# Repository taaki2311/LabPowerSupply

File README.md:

# ECE_492-3_Topic_1

This git repository is for ECE/RS 492/3 Topic 1: Lab Power Supply in Spring to Fall 2022.

## Getting started

To make it easy for you to get started with GitLab, here's a list of recommended next steps.

Already a pro? Just edit this README.md and make it your own. Want to make it easy? [Use the template at the bottom](#editing-this-readme)!

## Add your files

- [ ] [Create](https://docs.gitlab.com/ee/user/project/repository/web_editor.html#create-a-file) or [upload](https://docs.gitlab.com/ee/user/project/repository/web_editor.html#upload-a-file) files
- [ ] [Add files using the command line](https://docs.gitlab.com/ee/gitlab-basics/add-file.html#add-a-file-using-the-command-line) or push an existing Git repository with the following command:

```
cd existing_repo
git remote add origin https://git.gmu.edu/tsingh8/ece_492-3_topic_1.git
git branch -M main
git push -uf origin main
```

## Integrate with your tools

- [ ] [Set up project integrations](https://git.gmu.edu/tsingh8/ece_492-3_topic_1/-/settings/integrations)

## Collaborate with your team

- [ ] [Invite team members and collaborators](https://docs.gitlab.com/ee/user/project/members/)
- [ ] [Create a new merge request](https://docs.gitlab.com/ee/user/project/merge_requests/creating_merge_requests.html)
- [ ] [Automatically close issues from merge requests](https://docs.gitlab.com/ee/user/project/issues/managing_issues.html#closing-issues-automatically)
- [ ] [Enable merge request approvals](https://docs.gitlab.com/ee/user/project/merge_requests/approvals/)
- [ ] [Automatically merge when pipeline succeeds](https://docs.gitlab.com/ee/user/project/merge_requests/merge_when_pipeline_succeeds.html)

## Test and Deploy

Use the built-in continuous integration in GitLab.

- [ ] [Get started with GitLab CI/CD](https://docs.gitlab.com/ee/ci/quick_start/index.html)
- [ ] [Analyze your code for known vulnerabilities with Static Application Security Testing(SAST)](https://docs.gitlab.com/ee/user/application_security/sast/)
- [ ] [Deploy to Kubernetes, Amazon EC2, or Amazon ECS using Auto Deploy](https://docs.gitlab.com/ee/topics/autodevops/requirements.html)
- [ ] [Use pull-based deployments for improved Kubernetes management](https://docs.gitlab.com/ee/user/clusters/agent/)
- [ ] [Set up protected environments](https://docs.gitlab.com/ee/ci/environments/protected_environments.html)

***

# Editing this README

When you're ready to make this README your own, just edit this file and use the handy template below (or feel free to structure it however you want - this is just a starting point!).  Thank you to [makeareadme.com](https://www.makeareadme.com/) for this template.

## Suggestions for a good README
Every project is different, so consider which of these sections apply to yours. The sections used in the template are suggestions for most open source projects. Also keep in mind that while a README can be too long and detailed, too long is better than too short. If you think your README is too long, consider utilizing another form of documentation rather than cutting out information.

## Name
Choose a self-explaining name for your project.

## Description
Let people know what your project can do specifically. Provide context and add a link to any reference visitors might be unfamiliar with. A list of Features or a Background subsection can also be added here. If there are alternatives to your project, this is a good place to list differentiating factors.

## Badges
On some READMEs, you may see small images that convey metadata, such as whether or not all the tests are passing for the project. You can use Shields to add some to your README. Many services also have instructions for adding a badge.

## Visuals
Depending on what you are making, it can be a good idea to include screenshots or even a video (you'll frequently see GIFs rather than actual videos). Tools like ttygif can help, but check out Asciinema for a more sophisticated method.

## Installation
Within a particular ecosystem, there may be a common way of installing things, such as using Yarn, NuGet, or Homebrew. However, consider the possibility that whoever is reading your README is a novice and would like more guidance. Listing specific steps helps remove ambiguity and gets people to using your project as quickly as possible. If it only runs in a specific context like a particular programming language version or operating system or has dependencies that have to be installed manually, also add a Requirements subsection.

## Usage
Use examples liberally, and show the expected output if you can. It's helpful to have inline the smallest example of usage that you can demonstrate, while providing links to more sophisticated examples if they are too long to reasonably include in the README.

## Support
Tell people where they can go to for help. It can be any combination of an issue tracker, a chat room, an email address, etc.

## Roadmap
If you have ideas for releases in the future, it is a good idea to list them in the README.

## Contributing
State if you are open to contributions and what your requirements are for accepting them.

For people who want to make changes to your project, it's helpful to have some documentation on how to get started. Perhaps there is a script that they should run or some environment variables that they need to set. Make these steps explicit. These instructions could also be useful to your future self.

You can also document commands to lint the code or run tests. These steps help to ensure high code quality and reduce the likelihood that the changes inadvertently break something. Having instructions for running tests is especially helpful if it requires external setup, such as starting a Selenium server for testing in a browser.

## Authors and acknowledgment
Show your appreciation to those who have contributed to the project.

## License
For open source projects, say how it is licensed.

## Project status
If you have run out of energy or time for your project, put a note at the top of the README saying that development has slowed down or stopped completely. Someone may choose to fork your project or volunteer to step in as a maintainer or owner, allowing your project to keep going. You can also make an explicit request for maintainers.

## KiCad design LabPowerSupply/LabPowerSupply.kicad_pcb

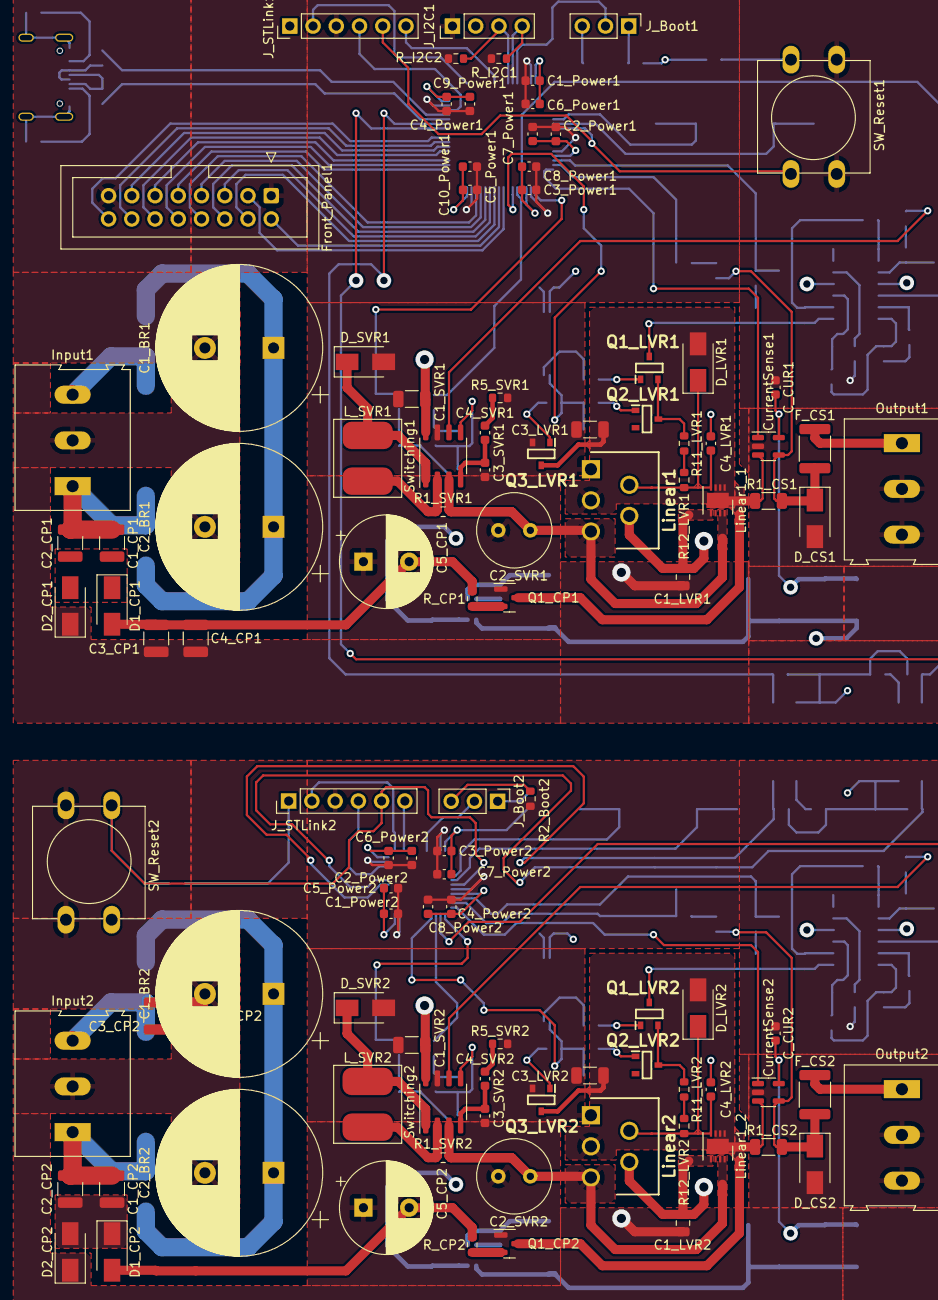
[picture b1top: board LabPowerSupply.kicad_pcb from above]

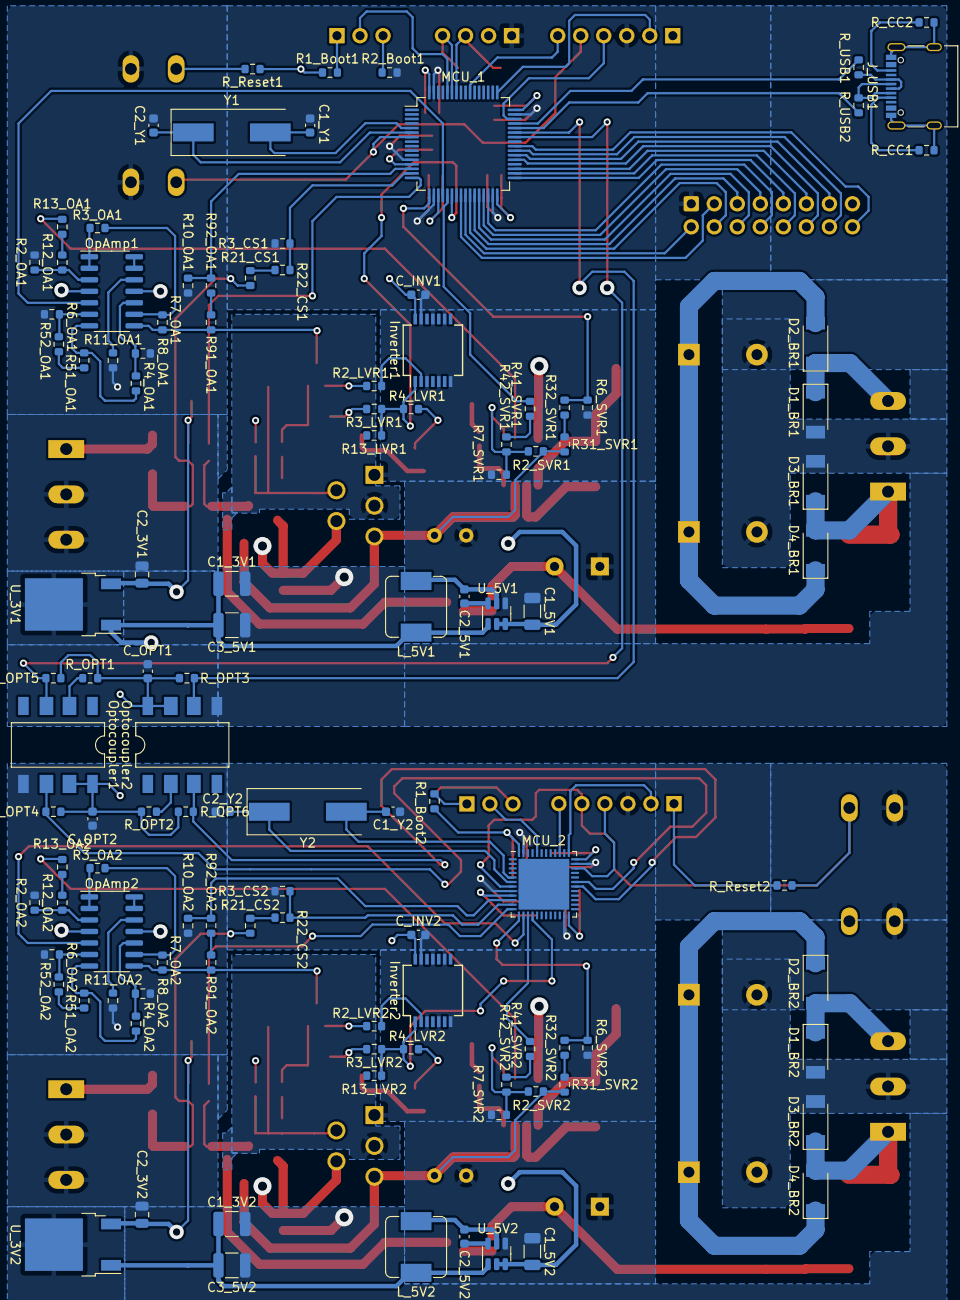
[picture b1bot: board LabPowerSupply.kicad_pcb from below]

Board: 4 copper layers, 219 parts (114 on the bottom side), 147 nets.

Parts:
C1_3V1, C1_3V2, C1_CP1, C1_CP2, C2_CP1, C2_CP2, C3_5V1, C3_5V2, C3_CP1, C3_CP2, C4_CP1, C4_CP2: 22u; C_1210_3225Metric
C1_5V1, C1_5V2, C1_SVR1, C1_SVR2, C3_LVR1, C3_LVR2: 10u; C_1206_3216Metric
C1_BR1, C1_BR2, C2_BR1, C2_BR2: 6.8m; CP_Radial_D18.0mm_P7.50mm
C1_LVR1, C1_LVR2: 4.7u; C_0805_2012Metric
C1_Power1, C1_Power2, C2_Power1, C2_Power2, C3_Power1, C3_Power2, C4_Power1, C4_Power2, C5_Power1: 1u; C_0603_1608Metric
C1_Y1, C1_Y2, C2_Y1, C2_Y2, C4_LVR1, C4_LVR2: 20p; C_0603_1608Metric
C2_3V1, C2_3V2: 2.2u; C_0805_2012Metric
C2_5V1, C2_5V2, C5_Power2, C6_Power1, C6_Power2, C7_Power1, C7_Power2, C8_Power1, C8_Power2, C9_Power1, C10_Power1: 100n; C_0603_1608Metric
C2_SVR1, C2_SVR2: 100u; C_Radial_D8.0mm_H7.0mm_P3.50mm
C3_SVR1, C3_SVR2: 22n; C_0603_1608Metric
C4_SVR1, C4_SVR2: 220p; C_0603_1608Metric
C5_CP1, C5_CP2: 1m; CP_Radial_D10.0mm_P5.00mm
C_CUR1, C_CUR2: 100n; C_0603_1608Metric
C_INV1, C_INV2: 100n; C_0603_1608Metric
C_OPT1, C_OPT2: 100n; C_0603_1608Metric
CurrentSense1, CurrentSense2: INA180A1; SOT-23-5
D1_BR1, D1_BR2, D2_BR1, D2_BR2, D3_BR1, D3_BR2, D4_BR1, D4_BR2: PMEG4050EP; D_SOD-128
D1_CP1, D1_CP2, D2_CP1, D2_CP2: 1N4001; D_SMA
D_CS1, D_CS2: 1N4001; D_SMA
D_LVR1, D_LVR2: 1N4001; D_SMA
D_SVR1, D_SVR2: 1N4001; D_SMA
F_CS1, F_CS2: 290m; Fuse_1812_4532Metric
Front_Panel1: Conn_02x08_Counter_Clockwise; IDC-Header_2x08_P2.54mm_Vertical
Input1, Input2: Screw_Terminal_01x03; TerminalBlock_Altech_AK300-3_P5.00mm
Inverter1, Inverter2: 74AHC04; SSOP-14_5.3x6.2mm_P0.65mm
J_Boot1, J_Boot2: Conn_01x03_Male; PinHeader_1x03_P2.54mm_Vertical
J_I2C1: Conn_01x04_Male; PinHeader_1x04_P2.54mm_Vertical
J_STLink1, J_STLink2: Conn_01x06_Male; PinHeader_1x06_P2.54mm_Vertical
J_USB1: USB_C_Receptacle_USB2.0; USB_C_Receptacle_Palconn_UTC16-G
L_5V1, L_5V2: 4.7u; L_Sumida_CDMC6D28_7.25x6.5mm
L_SVR1, L_SVR2: 22u; L_Sumida_CR75
Linear1, Linear2: LT3083ET#PBF; TO170P457X1022X2306-5P
Linear1_1, Linear1_2: LT3080xDD; DFN-8-1EP_3x3mm_P0.5mm_EP1.66x2.38mm
MCU_1: STM32L151R6TxA; LQFP-64_10x10mm_P0.5mm
MCU_2: STM32L100C6UxA; QFN-48-1EP_7x7mm_P0.5mm_EP5.6x5.6mm
OpAmp1, OpAmp2: LM324; SOIC-14_3.9x8.7mm_P1.27mm
Optocoupler1, Optocoupler2: 6N137; PowerIntegrations_SMD-8
Output1, Output2: Screw_Terminal_01x03; TerminalBlock_Altech_AK300-3_P5.00mm
Q1_CP1, Q1_CP2: FMMT495TA; SOT-23
Q1_LVR1, Q1_LVR2, Q2_LVR1, Q2_LVR2, Q3_LVR1, Q3_LVR2: PJA3404_R1_00001; SOT95P240X110-3N
R1_Boot1, R1_Boot2, R2_Boot1, R2_Boot2, R5_SVR1, R5_SVR2: 5.1k; R_0603_1608Metric
R1_CS1, R1_CS2: 300m; R_1206_3216Metric
R1_SVR1, R1_SVR2: 180m; R_0603_1608Metric
R2_LVR1, R2_LVR2, R2_OA1, R2_OA2, R3_CS1, R3_CS2, R3_LVR1, R3_LVR2, R3_OA1, R3_OA2, R4_LVR1, R4_LVR2, R4_OA1, R4_OA2, R6_OA1, R6_OA2, R6_SVR1, R6_SVR2, R7_OA1, R7_OA2, R8_OA1, R8_OA2, R10_OA1, R10_OA2, R22_CS1, R22_CS2, R92_OA1, R92_OA2: 1k; R_0603_1608Metric
R2_SVR1, R2_SVR2, R11_OA1, R11_OA2, R13_LVR1, R13_LVR2: 10k; R_0603_1608Metric
R7_SVR1, R7_SVR2, R41_SVR1, R41_SVR2, R42_SVR1, R42_SVR2: 1.2k; R_0603_1608Metric
R11_LVR1, R11_LVR2, R12_LVR1, R12_LVR2, R12_OA1, R12_OA2, R13_OA1, R13_OA2, R21_CS1, R21_CS2, R31_SVR1, R31_SVR2, R32_SVR1, R32_SVR2, R51_OA1, R51_OA2, R52_OA1, R52_OA2, R91_OA1, R91_OA2: 2k; R_0603_1608Metric
R_CC1, R_CC2: 5.1k; R_0603_1608Metric
R_CP1, R_CP2: 1k; R_0603_1608Metric
R_I2C1, R_I2C2: 4.7k; R_0603_1608Metric
R_OPT1, R_OPT2: 470; R_0603_1608Metric
R_OPT3, R_OPT4, R_OPT5, R_OPT6: 10k; R_0603_1608Metric
R_Reset1, R_Reset2: 1k; R_0603_1608Metric
R_USB1, R_USB2: 22; R_0603_1608Metric
SW_Reset1, SW_Reset2: SW_MEC_5G; SW_PUSH-12mm
Switching1, Switching2: L6902D; SO-8_3.9x4.9mm_P1.27mm
U_3V1, U_3V2: LP2950-3.3_TO252; TO-252-2
U_5V1, U_5V2: AP63205WU; TSOT-23-6
Y1, Y2: 8M; Crystal_SMD_HC49-SD

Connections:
+3.3V: C1_Power1.2, C2_3V1.1, C2_Power1.2, C3_Power1.2, C4_Power1.2, C5_Power1.2, C6_Power1.2, C7_Power1.2, C8_Power1.2, C9_Power1.2, C10_Power1.2, C_CUR1.2, C_INV1.2, C_OPT1.2, CurrentSense1.5 (V+), Inverter1.14 (VCC), J_STLink1.1, MCU_1.13 (VDDA), MCU_1.19 (VDD), MCU_1.32 (VDD), MCU_1.48 (VDD), MCU_1.64 (VDD), Optocoupler2.7 (EN), Optocoupler2.8 (VCC), R1_Boot1.2, R_OPT1.1, R_OPT3.2, R_OPT5.1, R_Reset1.1, U_3V1.3 (VO)
+3.3VA: C1_Power2.2, C2_3V2.1, C2_Power2.2, C3_Power2.2, C4_Power2.2, C5_Power2.2, C6_Power2.2, C7_Power2.2, C8_Power2.2, C_CUR2.2, C_INV2.2, C_OPT2.2, CurrentSense2.5 (V+), Inverter2.14 (VCC), J_STLink2.1, MCU_2.9 (VDDA), MCU_2.24 (VDD), MCU_2.36 (VDD), MCU_2.48 (VDD), Optocoupler1.7 (EN), Optocoupler1.8 (VCC), R1_Boot2.1, R_OPT2.2, R_OPT4.2, R_OPT6.2, R_Reset2.1, U_3V2.3 (VO)
/Channel 1 Power Rails/5 Volts: C1_3V1.2, C3_5V1.2, J_I2C1.2, L_5V1.2, U_3V1.1 (VI), U_5V1.1 (FB)
/Channel Power Supply 1/AC 1: D1_BR1.1 (K), D2_BR1.2 (A), Input1.3
/Channel Power Supply 1/AC 2: C1_CP1.1, C2_CP1.1, D3_BR1.1 (K), D4_BR1.2 (A), Input1.1
/Channel Power Supply 1/ADC 1: MCU_1.17 (PA3), R6_SVR1.1, R32_SVR1.2
/Channel Power Supply 1/ADC 2: MCU_1.14 (PA0), R10_OA1.1, R92_OA1.2
/Channel Power Supply 1/ADC 3: CurrentSense1.1, MCU_1.16 (PA2)
/Channel Power Supply 1/ADC 4: MCU_1.15 (PA1), R3_CS1.1, R22_CS1.2
/Channel Power Supply 1/Charge Pump/Charge: C3_LVR1.1, CurrentSense1.3 (+), D_LVR1.2 (A), Linear1.3 (OUT), Linear1_1.1 (OUT), Linear1_1.2 (OUT), Linear1_1.3 (OUT), Linear1_1.9 (OUT), Q1_CP1.3 (C), Q3_LVR1.3 (D), R1_CS1.1
/Channel Power Supply 1/Charge Pump/Negative: C3_CP1.1, C4_CP1.1, C5_CP1.2, D1_CP1.2 (A), OpAmp1.11 (V-), R_CP1.1
/Channel Power Supply 1/Current Sense /Output: CurrentSense1.4 (-), D_CS1.1 (K), F_CS1.1, R1_CS1.2, R21_CS1.1
/Channel Power Supply 1/DAC 1: MCU_1.21 (PA5), R41_SVR1.2
/Channel Power Supply 1/DAC 2: MCU_1.20 (PA4), OpAmp1.5 (+)
/Channel Power Supply 1/Differential Op-Amp Circuit/3.3 Volts: R13_OA1.1, Switching1.6 (VREF)
/Channel Power Supply 1/Differential Op-Amp Circuit/Set Voltage: OpAmp1.8, Q1_LVR1.3 (D), R7_OA1.2, R91_OA1.1
/Channel Power Supply 1/Linear Voltage Regulator /Linear Input: C2_SVR1.1, Linear1.5 (IN), Linear1_1.7 (IN), Linear1_1.8 (IN), R1_SVR1.2, R2_SVR1.1, R31_SVR1.1, Switching1.3 (CS-)
/Channel Power Supply 1/On/Off: Inverter1.1, MCU_1.22 (PA6), R3_LVR1.2, R4_LVR1.2, R13_LVR1.2
/Channel Power Supply 1/Switching Voltage Regulator/FeedBack: R2_SVR1.2, R7_SVR1.2, R42_SVR1.1, Switching1.5 (FB)
/Channel Power Supply 2/AC 1: D1_BR2.1 (K), D2_BR2.2 (A), Input2.3
/Channel Power Supply 2/AC 2: C1_CP2.1, C2_CP2.1, D3_BR2.1 (K), D4_BR2.2 (A), Input2.1
/Channel Power Supply 2/ADC 1: MCU_2.13 (PA3), R6_SVR2.1, R32_SVR2.2
/Channel Power Supply 2/ADC 2: MCU_2.10 (PA0), R10_OA2.1, R92_OA2.2
/Channel Power Supply 2/ADC 3: CurrentSense2.1, MCU_2.12 (PA2)
/Channel Power Supply 2/ADC 4: MCU_2.11 (PA1), R3_CS2.1, R22_CS2.2
/Channel Power Supply 2/Charge Pump/Charge: C3_LVR2.1, CurrentSense2.3 (+), D_LVR2.2 (A), Linear1_2.1 (OUT), Linear1_2.2 (OUT), Linear1_2.3 (OUT), Linear1_2.9 (OUT), Linear2.3 (OUT), Q1_CP2.3 (C), Q3_LVR2.3 (D), R1_CS2.1
/Channel Power Supply 2/Charge Pump/Negative: C3_CP2.1, C4_CP2.1, C5_CP2.2, D1_CP2.2 (A), OpAmp2.11 (V-), R_CP2.1
/Channel Power Supply 2/Current Sense /Output: CurrentSense2.4 (-), D_CS2.1 (K), F_CS2.1, R1_CS2.2, R21_CS2.1
/Channel Power Supply 2/DAC 1: MCU_2.15 (PA5), R41_SVR2.2
/Channel Power Supply 2/DAC 2: MCU_2.14 (PA4), OpAmp2.5 (+)
/Channel Power Supply 2/Differential Op-Amp Circuit/3.3 Volts: R13_OA2.1, Switching2.6 (VREF)
/Channel Power Supply 2/Differential Op-Amp Circuit/Set Voltage: OpAmp2.8, Q1_LVR2.3 (D), R7_OA2.2, R91_OA2.1
/Channel Power Supply 2/Linear Voltage Regulator /Linear Input: C2_SVR2.1, Linear1_2.7 (IN), Linear1_2.8 (IN), Linear2.5 (IN), R1_SVR2.2, R2_SVR2.1, R31_SVR2.1, Switching2.3 (CS-)
/Channel Power Supply 2/On/Off: Inverter2.1, MCU_2.16 (PA6), R3_LVR2.2, R4_LVR2.2, R13_LVR2.2
/Channel Power Supply 2/Switching Voltage Regulator/FeedBack: R2_SVR2.2, R7_SVR2.2, R42_SVR2.1, Switching2.5 (FB)
/Optocouplers/RX 1: MCU_1.43 (PA10), Optocoupler2.6 (VO), R_OPT3.1
/Optocouplers/RX 2: MCU_2.31 (PA10), Optocoupler1.6 (VO), R_OPT4.1
/Optocouplers/TX1: MCU_1.42 (PA9), Optocoupler1.3 (C), R_OPT5.2
/Optocouplers/TX 2: MCU_2.30 (PA9), Optocoupler2.3 (C), R_OPT6.1
/Primary Controller/I2C SCL: J_I2C1.4, MCU_1.59 (PB7), R_I2C1.1
/Primary Controller/I2C SDA: J_I2C1.3, MCU_1.58 (PB6), R_I2C2.1
/Primary Controller/SWO: J_STLink1.6, MCU_1.55 (PB3)
/Primary Controller/SW_CLK: J_STLink1.2, MCU_1.49 (PA14)
/Primary Controller/SW_DIO: J_STLink1.4, MCU_1.46 (PA13)
GND1: C1_3V1.1, C1_5V1.1, C1_BR1.2, C1_LVR1.1, C1_Power1.1, C1_SVR1.2, C1_Y1.1, C2_3V1.2, C2_BR1.2, C2_Power1.1, C2_SVR1.2, C2_Y1.1, C3_5V1.1, C3_CP1.2, C3_LVR1.2, C3_Power1.1, C3_SVR1.2, C4_CP1.2, C4_LVR1.2, C4_Power1.1, C5_CP1.1, C5_Power1.1, C6_Power1.1, C7_Power1.1, C8_Power1.1, C9_Power1.1, C10_Power1.1, C_CUR1.1, C_INV1.1, C_OPT1.1, CurrentSense1.2 (GND), D1_BR1.2 (A), D2_CP1.1 (K), D3_BR1.2 (A), D_CS1.2 (A), D_SVR1.2 (A), Front_Panel1.1, Front_Panel1.15, Input1.2, Inverter1.3, Inverter1.5, Inverter1.7 (GND), Inverter1.9, Inverter1.11, Inverter1.13, J_I2C1.1, J_STLink1.3, Linear1.1 (NC), MCU_1.12 (VSSA), MCU_1.18 (VSS), MCU_1.31 (VSS), MCU_1.47 (VSS), MCU_1.63 (VSS), Optocoupler2.5 (GND), Output1.2, Output1.3, Q1_CP1.2 (B), Q2_LVR1.2 (S), Q3_LVR1.2 (S), R2_Boot1.2, R2_OA1.2, R3_CS1.2, R5_SVR1.2, R6_OA1.2, R6_SVR1.2, R7_SVR1.1, R8_OA1.2, R10_OA1.2, R11_OA1.1, R13_LVR1.1, R_I2C1.2, R_I2C2.2, SW_Reset1.1, Switching1.7 (GND), U_3V1.2 (GND), U_5V1.4 (GND)
GND2: C1_3V2.1, C1_5V2.1, C1_BR2.2, C1_LVR2.1, C1_Power2.1, C1_SVR2.2, C1_Y2.1, C2_3V2.2, C2_BR2.2, C2_Power2.1, C2_SVR2.2, C2_Y2.1, C3_5V2.1, C3_CP2.2, C3_LVR2.2, C3_Power2.1, C3_SVR2.2, C4_CP2.2, C4_LVR2.2, C4_Power2.1, C5_CP2.1, C5_Power2.1, C6_Power2.1, C7_Power2.1, C8_Power2.1, C_CUR2.1, C_INV2.1, C_OPT2.1, CurrentSense2.2 (GND), D1_BR2.2 (A), D2_CP2.1 (K), D3_BR2.2 (A), D_CS2.2 (A), D_SVR2.2 (A), Input2.2, Inverter2.3, Inverter2.5, Inverter2.7 (GND), Inverter2.9, Inverter2.11, Inverter2.13, J_STLink2.3, Linear2.1 (NC), MCU_2.8 (VSSA), MCU_2.23 (VSS), MCU_2.35 (VSS), MCU_2.47 (VSS), MCU_2.49 (VSS), Optocoupler1.5 (GND), Output2.2, Output2.3, Q1_CP2.2 (B), Q2_LVR2.2 (S), Q3_LVR2.2 (S), R2_Boot2.2, R2_OA2.2, R3_CS2.2, R5_SVR2.2, R6_OA2.2, R6_SVR2.2, R7_SVR2.1, R8_OA2.2, R10_OA2.2, R11_OA2.1, R13_LVR2.1, SW_Reset2.1, Switching2.7 (GND), U_3V2.2 (GND), U_5V2.4 (GND)
unnamed: C1_3V2.2, C3_5V2.2, L_5V2.2, U_3V2.1 (VI), U_5V2.1 (FB)
unnamed: C1_CP1.2, C2_CP1.2, D1_CP1.1 (K), D2_CP1.2 (A)
unnamed: C1_CP2.2, C2_CP2.2, D1_CP2.1 (K), D2_CP2.2 (A)
unnamed: C1_Y1.2, MCU_1.5 (PH0), Y1.2
unnamed: C1_Y2.2, MCU_2.5 (PH0), Y2.2
unnamed: C2_5V1.1, L_5V1.1, U_5V1.5 (SW)
unnamed: C2_5V1.2, U_5V1.6 (BST)
unnamed: C2_5V2.1, L_5V2.1, U_5V2.5 (SW)
unnamed: C2_5V2.2, U_5V2.6 (BST)
unnamed: C2_Y1.2, MCU_1.6 (PH1), Y1.1
unnamed: C2_Y2.2, MCU_2.6 (PH1), Y2.1
unnamed: C3_SVR1.1, C4_SVR1.1, Switching1.4 (COMP)
unnamed: C3_SVR2.1, C4_SVR2.1, Switching2.4 (COMP)
unnamed: C4_LVR1.1, D_LVR1.1 (K), Linear1.2 (SET), Linear1_1.4 (SET), R12_LVR1.1
unnamed: C4_LVR2.1, D_LVR2.1 (K), Linear1_2.4 (SET), Linear2.2 (SET), R12_LVR2.1
unnamed: C4_SVR1.2, R5_SVR1.1
unnamed: C4_SVR2.2, R5_SVR2.1
unnamed: D_SVR1.1 (K), L_SVR1.1, Switching1.1 (OUT)
unnamed: D_SVR2.1 (K), L_SVR2.1, Switching2.1 (OUT)
unnamed: F_CS1.2, Output1.1
unnamed: F_CS2.2, Output2.1
unnamed: Front_Panel1.2, MCU_1.25 (PC5)
unnamed: Front_Panel1.3, MCU_1.24 (PC4)
unnamed: Front_Panel1.4, MCU_1.26 (PB0)
unnamed: Front_Panel1.5, MCU_1.27 (PB1)
unnamed: Front_Panel1.6, MCU_1.28 (PB2)
unnamed: Front_Panel1.7, MCU_1.29 (PB10)
unnamed: Front_Panel1.8, MCU_1.30 (PB11)
unnamed: Front_Panel1.9, MCU_1.33 (PB12)
unnamed: Front_Panel1.10, MCU_1.34 (PB13)
unnamed: Front_Panel1.11, MCU_1.35 (PB14)
unnamed: Front_Panel1.12, MCU_1.37 (PC6)
unnamed: Front_Panel1.13, MCU_1.38 (PC7)
unnamed: Front_Panel1.14, MCU_1.39 (PC8)
unnamed: Front_Panel1.16, MCU_1.40 (PC9)
unnamed: Inverter1.2, R2_LVR1.2
unnamed: Inverter2.2, R2_LVR2.2
unnamed: J_Boot1.1, R1_Boot1.1
unnamed: J_Boot1.2, MCU_1.60 (BOOT0)
unnamed: J_Boot1.3, R2_Boot1.1
unnamed: J_Boot2.1, R1_Boot2.2
unnamed: J_Boot2.2, MCU_2.44 (BOOT0)
unnamed: J_Boot2.3, R2_Boot2.1
unnamed: J_STLink1.5, MCU_1.7 (NRST), R_Reset1.2, SW_Reset1.2
unnamed: J_STLink2.2, MCU_2.37 (PA14)
unnamed: J_STLink2.4, MCU_2.34 (PA13)
unnamed: J_STLink2.5, MCU_2.7 (NRST), R_Reset2.2, SW_Reset2.2
unnamed: J_STLink2.6, MCU_2.39 (PB3)
unnamed: J_USB1.A1 (GND), J_USB1.A12 (GND), J_USB1.B1 (GND), J_USB1.B12 (GND), J_USB1.S1 (SHIELD), R_CC1.2, R_CC2.2
unnamed: J_USB1.A5 (CC1), R_CC1.1
unnamed: J_USB1.A6 (D+), J_USB1.B6 (D+), R_USB1.2
unnamed: J_USB1.A7 (D-), J_USB1.B7 (D-), R_USB2.2
unnamed: J_USB1.B5 (CC2), R_CC2.1
unnamed: L_SVR1.2, R1_SVR1.1, Switching1.2 (CS+)
unnamed: L_SVR2.2, R1_SVR2.1, Switching2.2 (CS+)
unnamed: MCU_1.44 (PA11), R_USB2.1
unnamed: MCU_1.45 (PA12), R_USB1.1
unnamed: OpAmp1.1, OpAmp1.2 (-), R3_OA1.1
unnamed: OpAmp1.3 (+), R2_OA1.1, R12_OA1.2
unnamed: OpAmp1.6 (-), R6_OA1.1, R52_OA1.2
unnamed: OpAmp1.7, R4_OA1.1, R51_OA1.1
unnamed: OpAmp1.9 (-), R3_OA1.2, R7_OA1.1
unnamed: OpAmp1.10 (+), R4_OA1.2, R8_OA1.1
unnamed: OpAmp1.12 (+), R11_OA1.2
unnamed: OpAmp1.13 (-), OpAmp1.14
unnamed: OpAmp2.1, OpAmp2.2 (-), R3_OA2.1
unnamed: OpAmp2.3 (+), R2_OA2.1, R12_OA2.2
unnamed: OpAmp2.6 (-), R6_OA2.1, R52_OA2.2
unnamed: OpAmp2.7, R4_OA2.1, R51_OA2.1
unnamed: OpAmp2.9 (-), R3_OA2.2, R7_OA2.1
unnamed: OpAmp2.10 (+), R4_OA2.2, R8_OA2.1
unnamed: OpAmp2.12 (+), R11_OA2.2
unnamed: OpAmp2.13 (-), OpAmp2.14
unnamed: Optocoupler1.2 (A), R_OPT1.2
unnamed: Optocoupler2.2 (A), R_OPT2.1
unnamed: Q1_CP1.1 (E), R_CP1.2
unnamed: Q1_CP2.1 (E), R_CP2.2
unnamed: Q1_LVR1.1 (G), R2_LVR1.1
unnamed: Q1_LVR1.2 (S), Q2_LVR1.3 (D), R11_LVR1.2
unnamed: Q1_LVR2.1 (G), R2_LVR2.1
unnamed: Q1_LVR2.2 (S), Q2_LVR2.3 (D), R11_LVR2.2
unnamed: Q2_LVR1.1 (G), R3_LVR1.1
unnamed: Q2_LVR2.1 (G), R3_LVR2.1
unnamed: Q3_LVR1.1 (G), R4_LVR1.1
unnamed: Q3_LVR2.1 (G), R4_LVR2.1
unnamed: R11_LVR1.1, R12_LVR1.2
unnamed: R11_LVR2.1, R12_LVR2.2
unnamed: R12_OA1.1, R13_OA1.2
unnamed: R12_OA2.1, R13_OA2.2
unnamed: R21_CS1.2, R22_CS1.1
unnamed: R21_CS2.2, R22_CS2.1
unnamed: R31_SVR1.2, R32_SVR1.1
unnamed: R31_SVR2.2, R32_SVR2.1
unnamed: R41_SVR1.1, R42_SVR1.2
unnamed: R41_SVR2.1, R42_SVR2.2
unnamed: R51_OA1.2, R52_OA1.1
unnamed: R51_OA2.2, R52_OA2.1
unnamed: R91_OA1.2, R92_OA1.1
unnamed: R91_OA2.2, R92_OA2.1
VCC: C1_5V1.2, C1_BR1.1, C1_LVR1.2, C1_SVR1.1, C2_BR1.1, D2_BR1.1 (K), D4_BR1.1 (K), Linear1.4 (VCONTROL), Linear1_1.5 (VCONTROL), OpAmp1.4 (V+), Switching1.8 (VCC), U_5V1.2 (EN), U_5V1.3 (IN)
VDD: C1_5V2.2, C1_BR2.1, C1_LVR2.2, C1_SVR2.1, C2_BR2.1, D2_BR2.1 (K), D4_BR2.1 (K), Linear1_2.5 (VCONTROL), Linear2.4 (VCONTROL), OpAmp2.4 (V+), Switching2.8 (VCC), U_5V2.2 (EN), U_5V2.3 (IN)

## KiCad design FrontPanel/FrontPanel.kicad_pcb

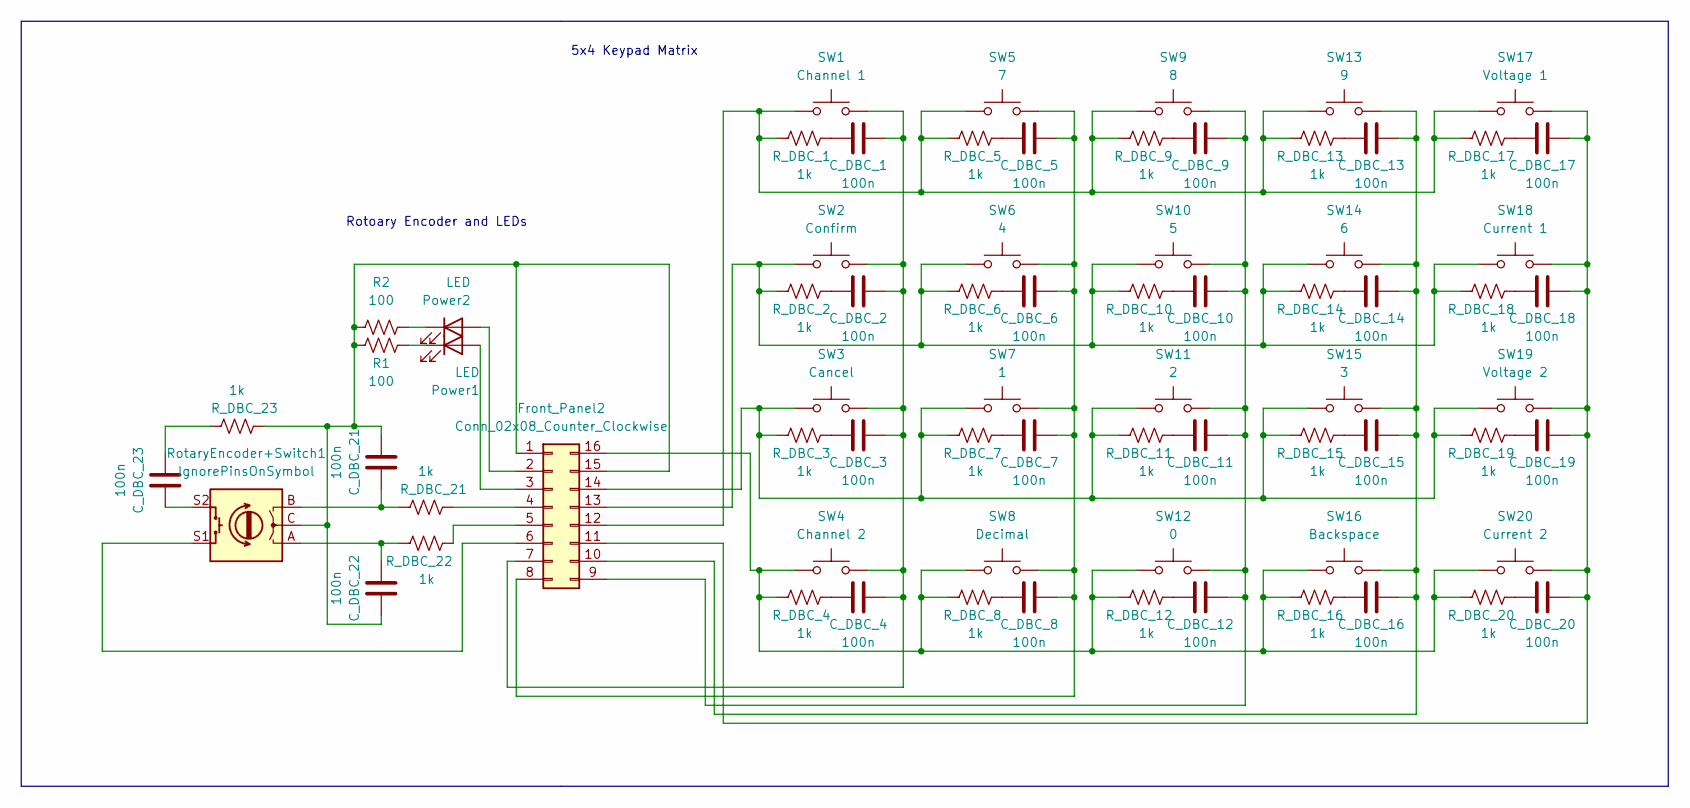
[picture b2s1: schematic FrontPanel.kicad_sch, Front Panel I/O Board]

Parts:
C_DBC_1, C_DBC_2, C_DBC_3, C_DBC_4, C_DBC_5, C_DBC_6, C_DBC_7, C_DBC_8, C_DBC_9, C_DBC_10, C_DBC_11, C_DBC_12, C_DBC_13, C_DBC_14, C_DBC_15, C_DBC_16, C_DBC_17, C_DBC_18, C_DBC_19, C_DBC_20, C_DBC_21, C_DBC_22, C_DBC_23: 100n; C_0603_1608Metric
Front_Panel2: Conn_02x08_Counter_Clockwise; IDC-Header_2x08_P2.54mm_Vertical
Power1, Power2: LED; LED_0603_1608Metric
R1, R2: 100; R_0603_1608Metric
R_DBC_1, R_DBC_2, R_DBC_3, R_DBC_4, R_DBC_5, R_DBC_6, R_DBC_7, R_DBC_8, R_DBC_9, R_DBC_10, R_DBC_11, R_DBC_12, R_DBC_13, R_DBC_14, R_DBC_15, R_DBC_16, R_DBC_17, R_DBC_18, R_DBC_19, R_DBC_20, R_DBC_21, R_DBC_22, R_DBC_23: 1k; R_0603_1608Metric
RotaryEncoder+Switch1: IgnorePinsOnSymbol; RotaryEncoder_Alps_EC11E-Switch_Vertical_H20mm
SW1: Channel 1; SW_PUSH-12mm
SW2: Confirm; SW_PUSH-12mm
SW3: Cancel; SW_PUSH-12mm
SW4: Channel 2; SW_PUSH-12mm
SW5: 7; SW_PUSH-12mm
SW6: 4; SW_PUSH-12mm
SW7: 1; SW_PUSH-12mm
SW8: Decimal; SW_PUSH-12mm
SW9: 8; SW_PUSH-12mm
SW10: 5; SW_PUSH-12mm
SW11: 2; SW_PUSH-12mm
SW12: 0; SW_PUSH-12mm
SW13: 9; SW_PUSH-12mm
SW14: 6; SW_PUSH-12mm
SW15: 3; SW_PUSH-12mm
SW16: Backspace; SW_PUSH-12mm
SW17: Voltage 1; SW_PUSH-12mm
SW18: Current 1; SW_PUSH-12mm
SW19: Voltage 2; SW_PUSH-12mm
SW20: Current 2; SW_PUSH-12mm

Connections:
unnamed: C_DBC_1.1, R_DBC_1.2
unnamed: C_DBC_1.2, C_DBC_2.2, C_DBC_3.2, C_DBC_4.2, Front_Panel2.7, SW1.2, SW2.2, SW3.2, SW4.2
unnamed: C_DBC_2.1, R_DBC_2.2
unnamed: C_DBC_3.1, R_DBC_3.2
unnamed: C_DBC_4.1, R_DBC_4.2
unnamed: C_DBC_5.1, R_DBC_5.2
unnamed: C_DBC_5.2, C_DBC_6.2, C_DBC_7.2, C_DBC_8.2, Front_Panel2.8, SW5.2, SW6.2, SW7.2, SW8.2
unnamed: C_DBC_6.1, R_DBC_6.2
unnamed: C_DBC_7.1, R_DBC_7.2
unnamed: C_DBC_8.1, R_DBC_8.2
unnamed: C_DBC_9.1, R_DBC_9.2
unnamed: C_DBC_10.1, R_DBC_10.2
unnamed: C_DBC_9.2, C_DBC_10.2, C_DBC_11.2, C_DBC_12.2, Front_Panel2.9, SW9.2, SW10.2, SW11.2, SW12.2
unnamed: C_DBC_11.1, R_DBC_11.2
unnamed: C_DBC_12.1, R_DBC_12.2
unnamed: C_DBC_13.1, R_DBC_13.2
unnamed: C_DBC_13.2, C_DBC_14.2, C_DBC_15.2, C_DBC_16.2, Front_Panel2.10, SW13.2, SW14.2, SW15.2, SW16.2
unnamed: C_DBC_14.1, R_DBC_14.2
unnamed: C_DBC_15.1, R_DBC_15.2
unnamed: C_DBC_16.1, R_DBC_16.2
unnamed: C_DBC_17.1, R_DBC_17.2
unnamed: C_DBC_18.1, R_DBC_18.2
unnamed: C_DBC_19.1, R_DBC_19.2
unnamed: C_DBC_20.1, R_DBC_20.2
unnamed: C_DBC_21.1, C_DBC_22.2, Front_Panel2.1, Front_Panel2.15, R1.2, R2.2, R_DBC_23.1, RotaryEncoder+Switch1.C
unnamed: C_DBC_21.2, R_DBC_21.2, RotaryEncoder+Switch1.B
unnamed: C_DBC_22.1, R_DBC_22.1, RotaryEncoder+Switch1.A
unnamed: C_DBC_23.1, R_DBC_23.2
unnamed: C_DBC_23.2, RotaryEncoder+Switch1.S2
unnamed: Front_Panel2.2, Power2.2 (A)
unnamed: Front_Panel2.3, Power1.2 (A)
unnamed: Front_Panel2.4, R_DBC_21.1
unnamed: Front_Panel2.5, R_DBC_22.2
unnamed: Front_Panel2.6, RotaryEncoder+Switch1.S1
unnamed: C_DBC_17.2, C_DBC_18.2, C_DBC_19.2, C_DBC_20.2, Front_Panel2.11, SW17.2, SW18.2, SW19.2, SW20.2
unnamed: Power1.1 (K), R1.1
unnamed: Power2.1 (K), R2.1
unnamed: Front_Panel2.12, R_DBC_1.1, R_DBC_5.1, R_DBC_9.1, R_DBC_13.1, R_DBC_17.1, SW1.1, SW5.1, SW9.1, SW13.1, SW17.1
unnamed: Front_Panel2.13, R_DBC_2.1, R_DBC_6.1, R_DBC_10.1, R_DBC_14.1, R_DBC_18.1, SW2.1, SW6.1, SW10.1, SW14.1, SW18.1
unnamed: Front_Panel2.14, R_DBC_3.1, R_DBC_7.1, R_DBC_11.1, R_DBC_15.1, R_DBC_19.1, SW3.1, SW7.1, SW11.1, SW15.1, SW19.1
unnamed: Front_Panel2.16, R_DBC_4.1, R_DBC_8.1, R_DBC_12.1, R_DBC_16.1, R_DBC_20.1, SW4.1, SW8.1, SW12.1, SW16.1, SW20.1

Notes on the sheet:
Rotoary Encoder and LEDs
5x4 Keypad Matrix

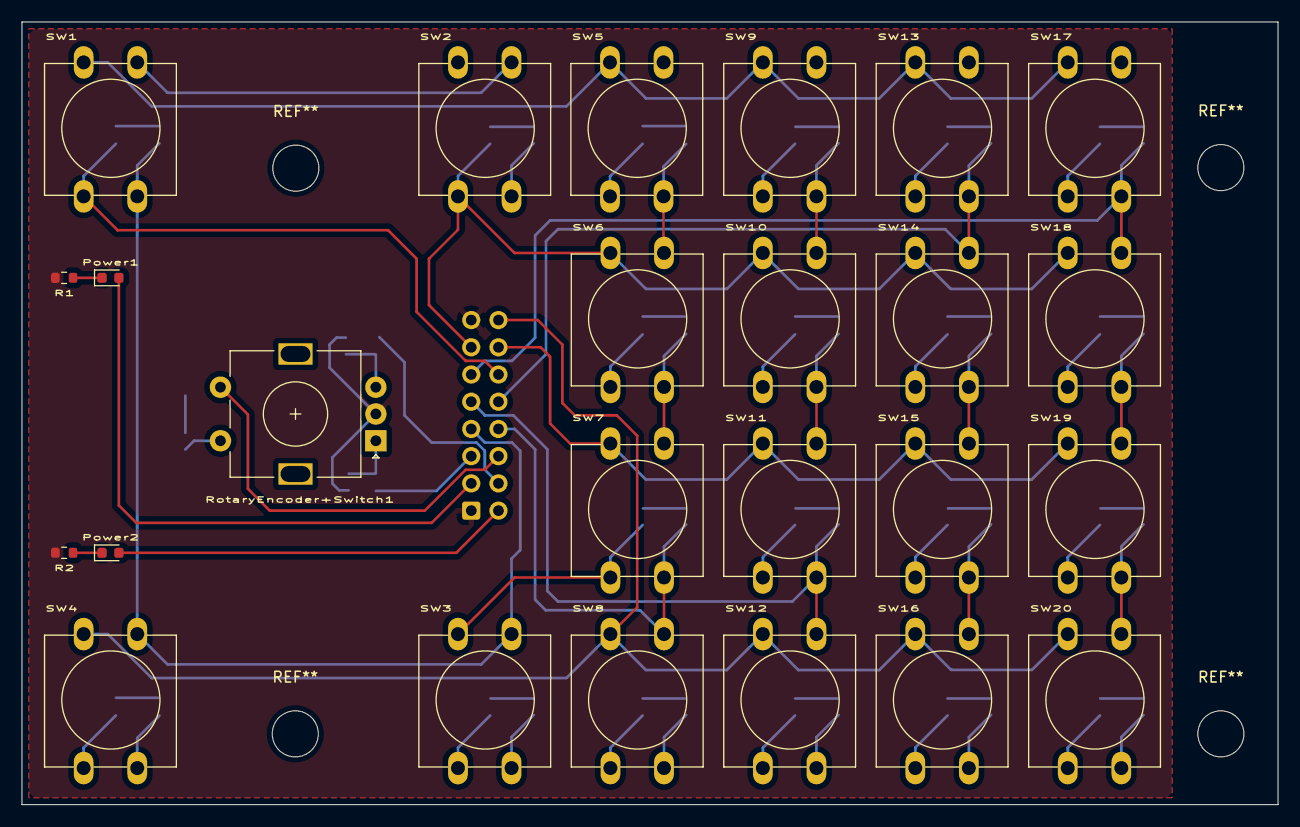
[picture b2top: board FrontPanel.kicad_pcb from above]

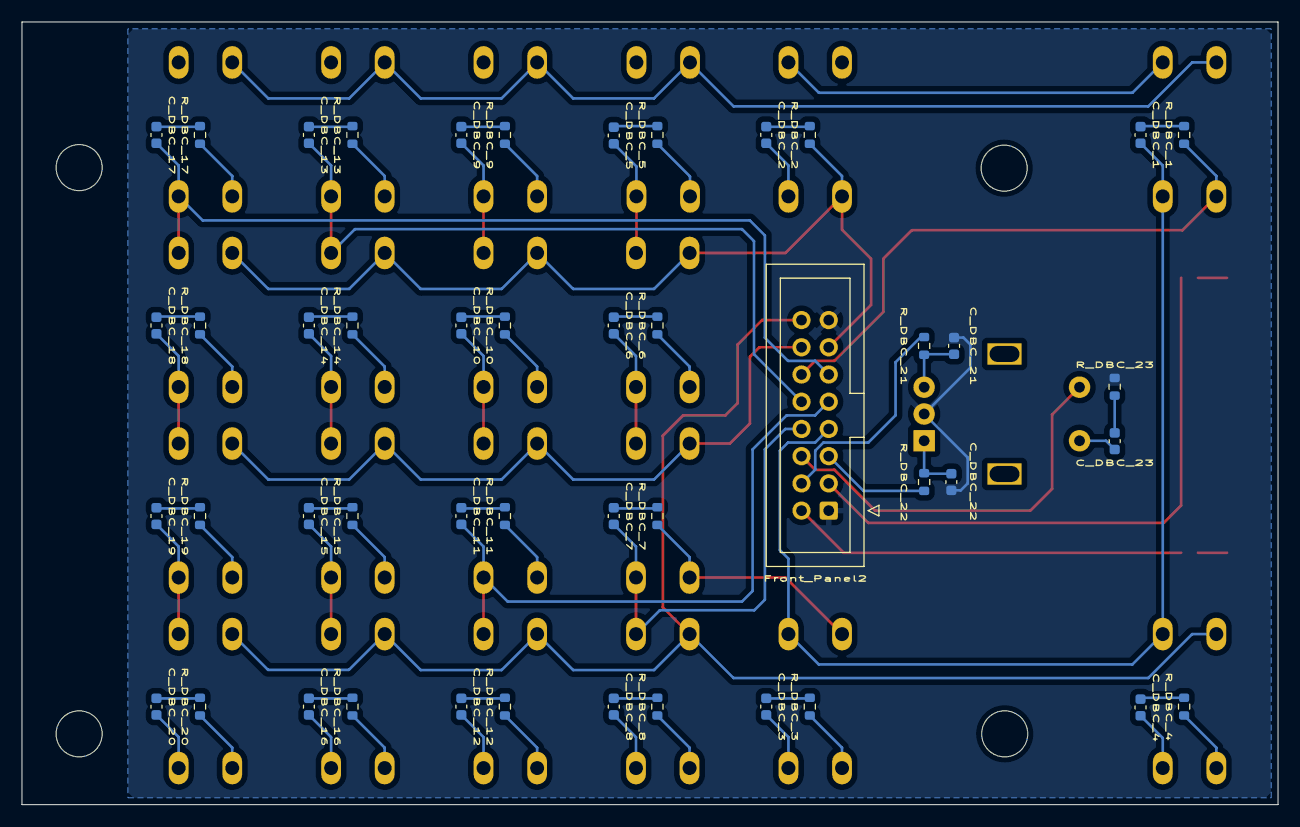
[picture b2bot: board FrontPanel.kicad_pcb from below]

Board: 2 copper layers, 117.2 x 73.0 mm, 72 parts (47 on the bottom side), 41 nets.

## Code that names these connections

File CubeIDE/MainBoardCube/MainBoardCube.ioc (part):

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Mcu.Name=STM32L152R(6-8-B)TxA
Mcu.Package=LQFP64
Mcu.UserName=STM32L152RBTxA
PA0-WKUP1.Mode=IN0
PA0-WKUP1.Signal=ADC_IN0
PA1.Mode=IN1
PA1.Signal=ADC_IN1
PA10.Mode=Asynchronous
PA10.Signal=USART1_RX
PA11.Mode=Device
PA11.Signal=USB_DM
PA12.Mode=Device
PA12.Signal=USB_DP
PA13.Mode=Serial_Wire
PA13.Signal=SYS_JTMS-SWDIO
PA14.Mode=Serial_Wire
PA14.Signal=SYS_JTCK-SWCLK
PA15.GPIOParameters=GPIO_PuPd,GPIO_Label
PA15.GPIO_Label=Unused_Pin_11
PA15.GPIO_PuPd=GPIO_PULLDOWN
PA15.Signal=GPIO_Input
PA2.Mode=IN2
PA2.Signal=ADC_IN2
PA3.Mode=IN3
PA3.Signal=ADC_IN3
PA4.Signal=COMP_DAC1_group
PA5.Signal=COMP_DAC2_group
PA6.GPIOParameters=PinState,GPIO_Label
PA6.GPIO_Label=Channel Shutdown
PA6.PinState=GPIO_PIN_SET
PA6.Signal=GPIO_Output
PA7.GPIOParameters=GPIO_PuPd,GPIO_Label
PA7.GPIO_Label=Unused_Pin_8
PA7.GPIO_PuPd=GPIO_PULLDOWN
PA7.Signal=GPIO_Input
PA8.GPIOParameters=GPIO_PuPd,GPIO_Label
PA8.GPIO_Label=Unused_Pin_10
PA8.GPIO_PuPd=GPIO_PULLDOWN
PA8.Signal=GPIO_Input
PA9.Mode=Asynchronous
PA9.Signal=USART1_TX
PB0.GPIOParameters=GPIO_PuPd,GPIO_Label,GPIO_ModeDefaultEXTI
PB0.GPIO_Label=Rot_CLK
PB0.GPIO_ModeDefaultEXTI=GPIO_MODE_IT_RISING_FALLING
PB0.GPIO_PuPd=GPIO_PULLUP
PB0.Signal=GPXTI0
PB1.GPIOParameters=GPIO_PuPd,GPIO_Label
PB1.GPIO_Label=Rot_DT
PB1.GPIO_PuPd=GPIO_PULLUP
PB1.Signal=GPIO_Input
PB10.GPIOParameters=GPIO_PuPd,GPIO_Label,GPIO_ModeDefaultEXTI
PB10.GPIO_Label=Row_1
PB10.GPIO_ModeDefaultEXTI=GPIO_MODE_IT_FALLING
PB10.GPIO_PuPd=GPIO_PULLUP
PB10.Signal=GPXTI10
PB11.GPIOParameters=GPIO_PuPd,GPIO_Label,GPIO_ModeDefaultEXTI
PB11.GPIO_Label=Row_2
PB11.GPIO_ModeDefaultEXTI=GPIO_MODE_IT_FALLING
PB11.GPIO_PuPd=GPIO_PULLUP
PB11.Signal=GPXTI11
PB12.GPIOParameters=GPIO_PuPd,GPIO_Label,GPIO_ModeDefaultEXTI
PB12.GPIO_Label=Row_3
PB12.GPIO_ModeDefaultEXTI=GPIO_MODE_IT_FALLING
PB12.GPIO_PuPd=GPIO_PULLUP
PB12.Signal=GPXTI12
PB13.GPIOParameters=GPIO_PuPd,GPIO_Label,GPIO_ModeDefaultEXTI
PB13.GPIO_Label=Row_4
PB13.GPIO_ModeDefaultEXTI=GPIO_MODE_IT_FALLING
PB13.GPIO_PuPd=GPIO_PULLUP
PB13.Signal=GPXTI13
PB14.GPIOParameters=GPIO_PuPd,GPIO_Label,GPIO_ModeDefaultEXTI
PB14.GPIO_Label=Row_5
PB14.GPIO_ModeDefaultEXTI=GPIO_MODE_IT_FALLING
PB14.GPIO_PuPd=GPIO_PULLUP
PB14.Signal=GPXTI14
PB15.GPIOParameters=GPIO_PuPd,GPIO_Label
PB15.GPIO_Label=Unused_Pin_9
PB15.GPIO_PuPd=GPIO_PULLDOWN
PB15.Signal=GPIO_Input
PB2.GPIOParameters=GPIO_PuPd,GPIO_Label,GPIO_ModeDefaultEXTI
PB2.GPIO_Label=Rot_SW
PB2.GPIO_ModeDefaultEXTI=GPIO_MODE_IT_FALLING
PB2.GPIO_PuPd=GPIO_PULLUP
PB2.Signal=GPXTI2
PB3.GPIOParameters=GPIO_PuPd,GPIO_Label
PB3.GPIO_Label=Unused_Pin_16
PB3.GPIO_PuPd=GPIO_PULLDOWN
PB3.Signal=GPIO_Input
PB4.GPIOParameters=GPIO_PuPd,GPIO_Label
PB4.GPIO_Label=Unused_Pin_17
PB4.GPIO_PuPd=GPIO_PULLDOWN
PB4.Signal=GPIO_Input
PB5.GPIOParameters=GPIO_PuPd,GPIO_Label
PB5.GPIO_Label=Unused_Pin_18
PB5.GPIO_PuPd=GPIO_PULLDOWN
PB5.Signal=GPIO_Input
PB6.Mode=I2C
PB6.Signal=I2C1_SCL
PB7.Mode=I2C
PB7.Signal=I2C1_SDA
PB8.GPIOParameters=GPIO_PuPd,GPIO_Label
PB8.GPIO_Label=Unused_Pin_19
PB8.GPIO_PuPd=GPIO_PULLDOWN
PB8.Signal=GPIO_Input
PB9.GPIOParameters=GPIO_PuPd,GPIO_Label
PB9.GPIO_Label=Unused_Pin_20
PB9.GPIO_PuPd=GPIO_PULLDOWN
PB9.Signal=GPIO_Input
PC0.GPIOParameters=GPIO_PuPd,GPIO_Label
PC0.GPIO_Label=Unused_Pin_4
PC0.GPIO_PuPd=GPIO_PULLDOWN
PC0.Signal=GPIO_Input
PC1.GPIOParameters=GPIO_PuPd,GPIO_Label
PC1.GPIO_Label=Unused_Pin_5
PC1.GPIO_PuPd=GPIO_PULLDOWN
PC1.Signal=GPIO_Input
PC10.GPIOParameters=GPIO_PuPd,GPIO_Label
PC10.GPIO_Label=Unused_Pin_12
PC10.GPIO_PuPd=GPIO_PULLDOWN
PC10.Signal=GPIO_Input
PC11.GPIOParameters=GPIO_PuPd,GPIO_Label
PC11.GPIO_Label=Unused_Pin_13
PC11.GPIO_PuPd=GPIO_PULLDOWN
PC11.Signal=GPIO_Input
PC12.GPIOParameters=GPIO_PuPd,GPIO_Label
PC12.GPIO_Label=Unused_Pin_14
PC12.GPIO_PuPd=GPIO_PULLDOWN
PC12.Signal=GPIO_Input
PC13-WKUP2.GPIOParameters=GPIO_PuPd,GPIO_Label
PC13-WKUP2.GPIO_Label=Unused_Pin_1
PC13-WKUP2.GPIO_PuPd=GPIO_PULLDOWN
PC13-WKUP2.Signal=GPIO_Input
PC14-OSC32_IN.GPIOParameters=GPIO_PuPd,GPIO_Label
PC14-OSC32_IN.GPIO_Label=Unused_Pin_2
PC14-OSC32_IN.GPIO_PuPd=GPIO_PULLDOWN
PC14-OSC32_IN.Signal=GPIO_Input
PC15-OSC32_OUT.GPIOParameters=GPIO_PuPd,GPIO_Label
PC15-OSC32_OUT.GPIO_Label=Unused_Pin_3
PC15-OSC32_OUT.GPIO_PuPd=GPIO_PULLDOWN
PC15-OSC32_OUT.Signal=GPIO_Input
PC2.GPIOParameters=GPIO_PuPd,GPIO_Label
PC2.GPIO_Label=Unused_Pin_6
PC2.GPIO_PuPd=GPIO_PULLDOWN
PC2.Signal=GPIO_Input
PC3.GPIOParameters=GPIO_PuPd,GPIO_Label
PC3.GPIO_Label=Unused_Pin_7
PC3.GPIO_PuPd=GPIO_PULLDOWN
PC3.Signal=GPIO_Input
PC4.GPIOParameters=GPIO_Label
PC4.GPIO_Label=Status_LED_1
PC4.Signal=GPIO_Output
PC5.GPIOParameters=GPIO_Label
PC5.GPIO_Label=Status_LED_2
PC5.Signal=GPIO_Output
PC6.GPIOParameters=GPIO_Label
PC6.GPIO_Label=Col_1
PC6.Signal=GPIO_Output
PC7.GPIOParameters=GPIO_Label
PC7.GPIO_Label=Col_2
PC7.Signal=GPIO_Output
PC8.GPIOParameters=GPIO_Label
PC8.GPIO_Label=Col_3
PC8.Signal=GPIO_Output
PC9.GPIOParameters=GPIO_Label
PC9.GPIO_Label=Col_4
PC9.Signal=GPIO_Output
PD2.GPIOParameters=GPIO_PuPd,GPIO_Label
PD2.GPIO_Label=Unused_Pin_15
PD2.GPIO_PuPd=GPIO_PULLDOWN
PD2.Signal=GPIO_Input
PH0-OSC_IN.Mode=HSE-External-Oscillator
PH0-OSC_IN.Signal=RCC_OSC_IN
PH1-OSC_OUT.Mode=HSE-External-Oscillator
PH1-OSC_OUT.Signal=RCC_OSC_OUT
RCC.HSE_VALUE=8000000
RCC.SYSCLKFreq_VALUE=32000000
RCC.SYSCLKSource=RCC_SYSCLKSOURCE_PLLCLK
board=custom
